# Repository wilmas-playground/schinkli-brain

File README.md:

# Bewässerungssystem für Pflanzen auf ESP8266

This repository contains the source and manufacturing files for the controller board of 
a plant watering system named _schinkli_. The main concept of the system is to have a controller 
board and shields for it.

## schinkli brain

The controller board is named _schinkli brain_ and contains the footprint for an ESP12E, a voltage regulator and the pin header for attaching shields.

## Project URLs

Software: [schinkli-code](https://github.com/wilmas-playground/schinkli-code)

Controller: [schinkli-brain](https://github.com/wilmas-playground/schinkli-brain)

Pump Drivers: [schinkli-pump-shield](https://github.com/wilmas-playground/schinkli-pump-shield)

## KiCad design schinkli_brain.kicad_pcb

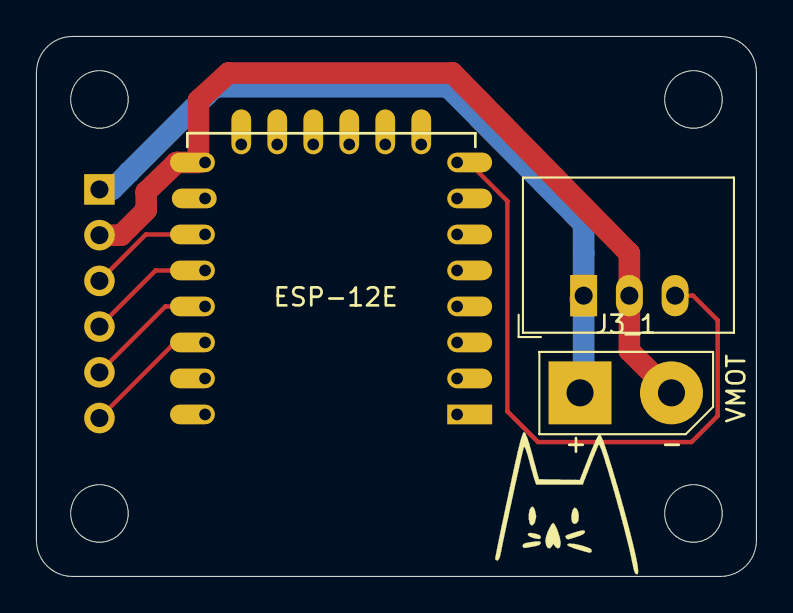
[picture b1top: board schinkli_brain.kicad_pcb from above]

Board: 2 copper layers, 40.0 x 30.0 mm, 8 parts (1 on the bottom side), 7 nets.

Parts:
J1: BridgeHeader; PinSocket_1x06_P2.54mm_Vertical
J3_1: VMOT; SolderWirePad_1x02_P5.08mm_Drill1.5mm
Q2: WE-FDSM3.3; Converter_DCDC_RECOM_R-78E-0.5_THT
U1: ESP-12E
hole1, hole2, hole3, hole4: MountingHole_3.2mm_M3

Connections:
+3V3: Q2.3, U1.8
DP1: J1.3, U1.11
DP2: J1.4, U1.12
DP3: J1.5, U1.13
DP4: J1.6, U1.14
GND: J1.2, J3_1.2, Q2.2, U1.9
VCC: J1.1, J3_1.1, Q2.1

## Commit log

2020-04-14 add project and production files v1
2020-04-15 add pcb images to readme
2020-04-15 resize images to reasonable size
2020-05-16 add 3d image and update readme
